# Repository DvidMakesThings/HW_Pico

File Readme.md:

# RePico

RePico is a custom-designed, feature-enhanced Raspberry Pi Pico-compatible board built for serious embedded developers. It keeps full compatibility with the RP2040 ecosystem while upgrading key components for cleaner analog performance, improved configurability, and professional-grade layout.

---

## 🔧 Key Hardware Features

- **USB-C** connector instead of Micro-USB for modern connectivity.
- **Low-noise 3.3V power supply** using `MIC5504-3.3YM5` 3.3V 300mA LDO (replaces noisy SMPS).
- **Selectable ADC Vref** via jumper:
  - External Vref input.
  - Internal precision 3.0V reference using `LM4040` + buffered by `MCP6001RT-I/OT`.
- **Selectable Vcore Supply** via jumper:
  - Use internal RP2040 regulator.
  - Or use onboard external 1.1V regulator based on `AP7335-WG-7` with adjustable output.
- **Adjustable Vcore Tuning** with trimpot-based feedback:

| Trimpot Resistance | Vcore Output |
|--------------------|---------------|
| 25k (max)          | ~1.00 V       |
| 12.5k (mid)        | ~1.18 V       |
| 0 Ω (min)          | ~1.24 V       |

- **128Mbit (16MB) QSPI Flash** — 4x more than the standard Pico.
- **RESET** and **BOOT** buttons included onboard.
- **4-layer impedance-controlled PCB** for signal integrity.

---

## PCB Stackup

- **Total Layers:** 4
- **Finished Thickness:** ~1.56 mm ±10%
- **Outer Copper Weight:** 1 oz
- **Inner Copper Weight:** 0.5 oz
- **Material:** JLC04161H-3313 (FR4)

### Layer Stackup

| Layer | Description       | Material                    | Thickness (mm) |
|-------|-------------------|-----------------------------|----------------|
| L1    | Signal (Top)      | Outer Copper 1 oz           | 0.0350         |
|       | Prepreg           | 3313 RC57%, 4.2 mil         | 0.0994         |
| L2    | Internal Plane    | Inner Copper 0.5 oz         | 0.0152         |
|       | Core              | 1.3 mm H/HOZ with copper     | 1.2650         |
| L3    | Internal Plane    | Inner Copper 0.5 oz         | 0.0152         |
|       | Prepreg           | 3313 RC57%, 4.2 mil         | 0.0994         |
| L4    | Signal (Bottom)   | Outer Copper 1 oz           | 0.0350         |
|       | **Total Thickness** |                             | **1.5588 mm**  |

---

## 📏 Controlled Impedance Configuration

| Impedance (Ω) | Type                     | Signal Layer | Top Ref | Bottom Ref | Trace Width (mm) | Trace Spacing (mm) | Trace to Copper (mm) |
|---------------|--------------------------|--------------|---------|-------------|-------------------|---------------------|-----------------------|
| 50            | Coplanar Single Ended    | L1           | /       | L2          | 0.1486            | /                   | 0.2032                |
| 90            | Coplanar Differential    | L1           | /       | L2          | 0.1488            | 0.1778              | 0.2032                |
| 90            | Coplanar Differential    | L4           | L3      | /           | 0.1488            | 0.1778              | 0.2032                |
| 50            | Coplanar Single Ended    | L4           | L3      | /           | 0.1486            | /                   | 0.2032                |

---

## 🧠 RP2040 Pinout Compatibility

All RP2040 GPIOs are exposed through 2.54mm castellated headers, maintaining full compatibility with the original Raspberry Pi Pico pinout. 

---

## Misc: Core Voltage & Overclocking

To overclock the MCU, it's possible to supply more than 1.1 V to the core.  
By default, **external core voltage generation** is enabled using the **AP7335-WG-7**, which is activated via **J1**.  
The output voltage is set by adjusting the **R1 trimpot**.

> ⚠️ It is safe — the voltage range is limited by design and cannot damage the MCU.

### Voltage Range (Set by Divider)

| R1 (Trimpot) | Total Resistance (R28 + R1) | VOUT (approx) |
|--------------|----------------------------|----------------|
| 25 kΩ (max)  | 47 kΩ                       | 1.02 V         |
| 12.5 kΩ      | 34.5 kΩ                     | 1.14 V         |
| 0 Ω (min)    | 22 kΩ                       | 1.22 V         |

### Use Cases

- **Low Power Mode:** R1 = 25 kΩ → ~1.02 V  
- **Default / Safe:** R1 = 12.5 kΩ → ~1.14 V  
- **High Performance / Overclocking:** R1 = 0 Ω → ~1.22 V  

### VOUT Behavior Across Temperatures and Trim Settings

The AP7335-WG-7 regulator is affected by temperature-dependent reference voltage (VREF), output voltage accuracy, and resistor tolerances.  
This section outlines the **worst-case VOUT values** at cold, normal, and hot temperatures, across all trimpot settings.

> ⚙️ **Calculation Parameters:**
> - VOUT Accuracy: ±2% (from AP7335-WG-7 datasheet)
> - VREF Variation: Based on VREF vs. Temperature graph  
>   - −50 °C → 0.89 V  
>   - 25 °C → 0.80 V  
>   - 125 °C → 0.782 V
> - Resistors used: 1% tolerance (R27 = 12 kΩ, R28 = 22 kΩ, R1 = 0–25 kΩ trimpot)

The RP2040's **absolute maximum core voltage is 1.3 V** — values exceeding this may cause damage.

---

### ❄️ Cold (–50 °C, VREF = 0.89 V)

**Max Trim (R1 = 25 kΩ, Rb = 47 kΩ)**  
VOUT: **1.090 V – 1.144 V** ✅ Safe

**Mid Trim (R1 = 12.5 kΩ, Rb = 34.5 kΩ)**  
VOUT: **1.170 V – 1.230 V** ✅ Safe

**Min Trim (R1 = 0 Ω, Rb = 22 kΩ)**  
VOUT: **1.339 V – 1.413 V** ❌ Danger – exceeds RP2040 1.3 V limit

---

### 🌤️ Normal (25 °C, VREF = 0.80 V)

**Max Trim (R1 = 25 kΩ, Rb = 47 kΩ)**  
VOUT: **0.980 V – 1.029 V** ✅ Safe

**Mid Trim (R1 = 12.5 kΩ, Rb = 34.5 kΩ)**  
VOUT: **1.051 V – 1.106 V** ✅ Safe

**Min Trim (R1 = 0 Ω, Rb = 22 kΩ)**  
VOUT: **1.201 V – 1.265 V** ✅ Safe

---

### 🔥 Hot (125 °C, VREF = 0.782 V)

**Max Trim (R1 = 25 kΩ, Rb = 47 kΩ)**  
VOUT: **0.958 V – 1.005 V** ✅ Safe

**Mid Trim (R1 = 12.5 kΩ, Rb = 34.5 kΩ)**  
VOUT: **1.028 V – 1.082 V** ✅ Safe

**Min Trim (R1 = 0 Ω, Rb = 22 kΩ)**  
VOUT: **1.180 V – 1.243 V** ✅ Safe

## License
This project is licensed under the GPL-3.0 License. See the [LICENSE](LICENSE) file for details.

## Contact
For questions or feedback:
- Email: [dvidmakesthing@gmail.com](mailto:dvidmakesthing@gmail.com)
- GitHub: [DvidMakesThings](https://github.com/DvidMakesThings)

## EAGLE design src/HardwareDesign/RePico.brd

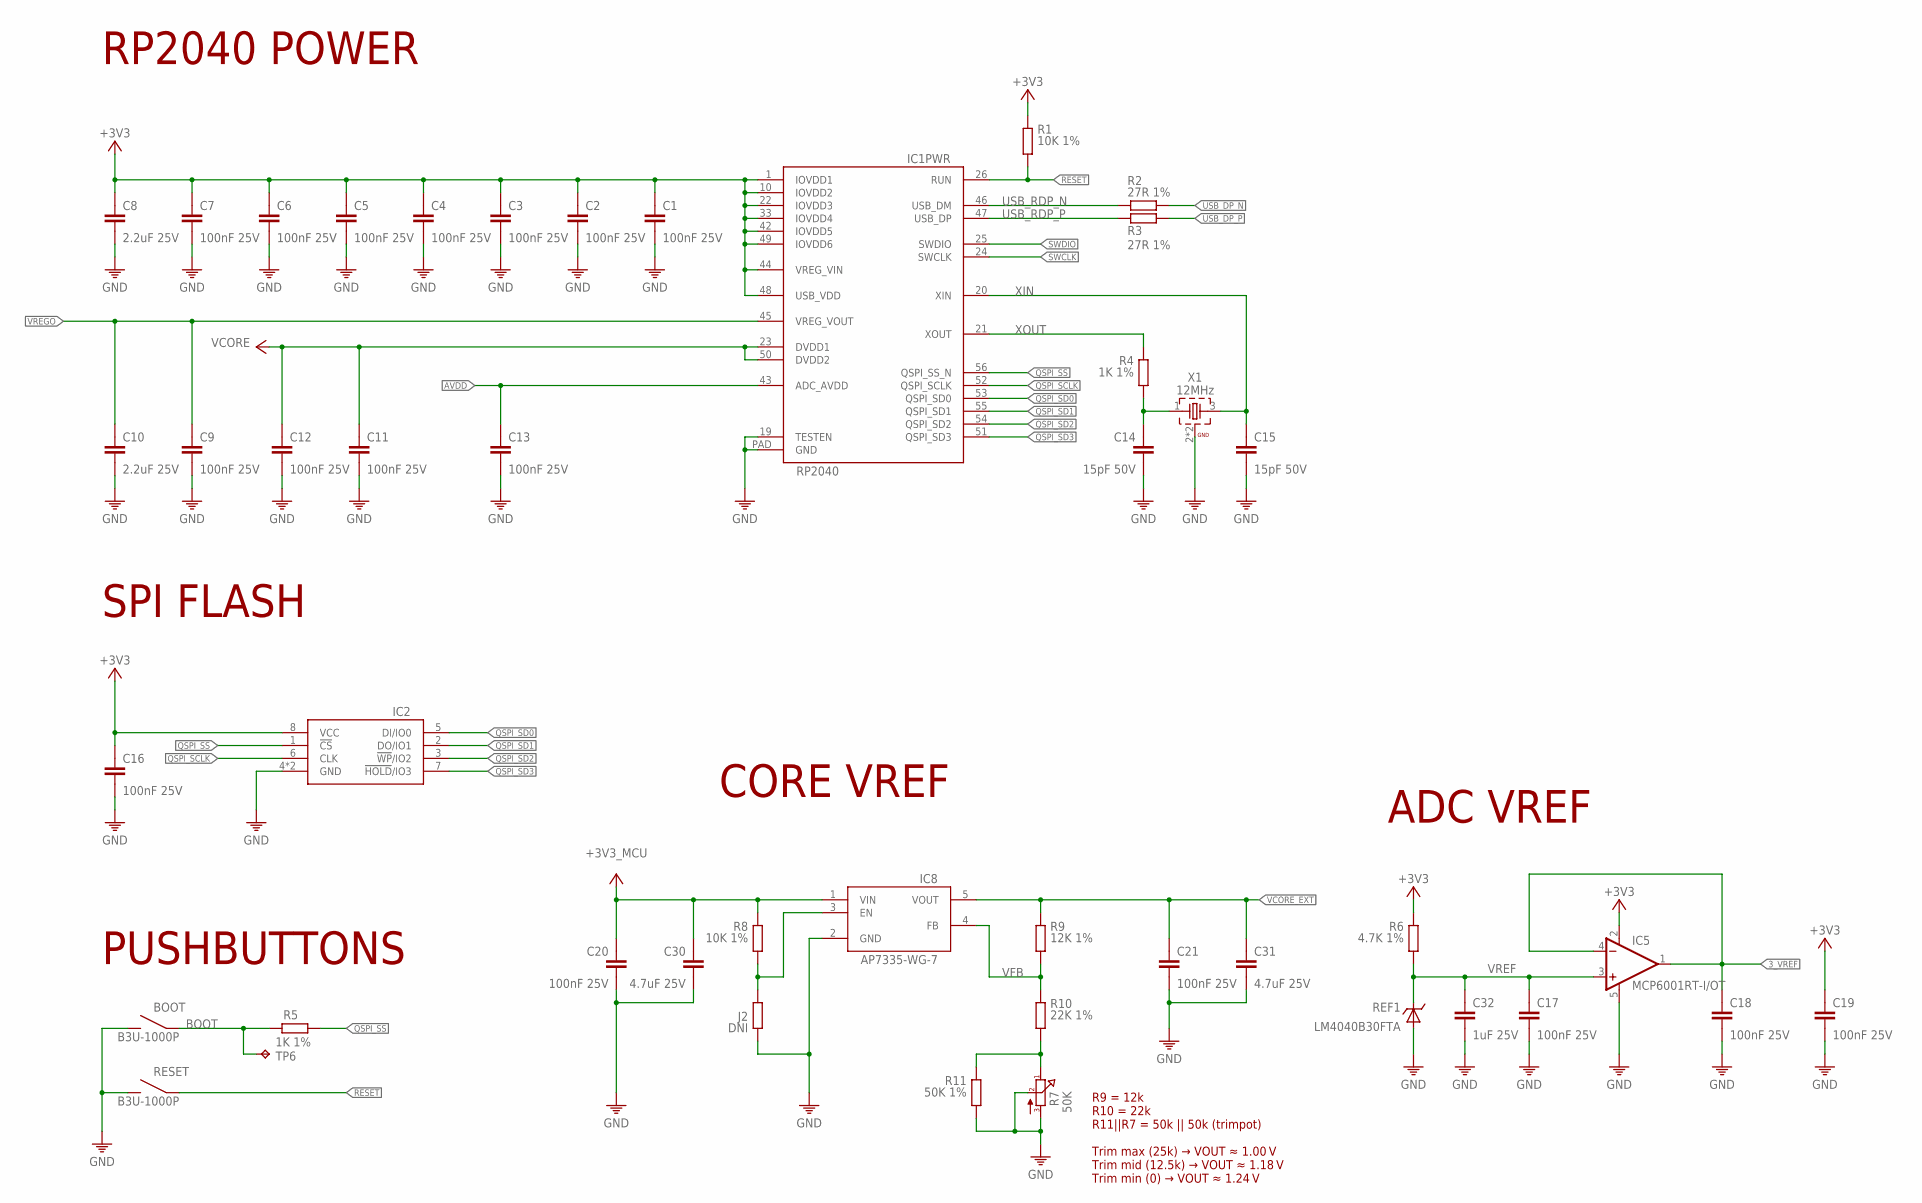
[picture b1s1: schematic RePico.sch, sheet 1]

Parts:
BOOT: B3U-1000P
C1, C2, C3, C4, C5, C6, C7, C9, C11, C12, C13, C16, C17, C18, C19, C20, C21: 100nF 25V; 0201
C8, C10: 2.2uF 25V; 0402
C14, C15: 15pF 50V; 0201
C30, C31: 4.7uF 25V; 0402
C32: 1uF 25V; 0402
IC1: RP2040; QFN56
IC2: W25Q128JVP; SON127P600X500X75-8N
IC5: MCP6001RT-I/OT; SOT23-5
IC8: AP7335-WG-7; SOT23-5
J2: DNI; R0201
R1, R8: 10K 1%; 0201
R2, R3: 27R 1%; 0201
R4, R5: 1K 1%; 0201
R6: 4.7K 1%; 0402
R7: 50K; SMD_TRIMM
R9: 12K 1%; 0201
R10: 22K 1%; 0201
R11: 50K 1%; 0402
REF1: LM4040B30FTA; SOT23
RESET: B3U-1000P
TP6: TPB1,27; B1,27
X1: 12MHz; WE-XTAL_CFPX-180

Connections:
3_VREF: C18.1, IC5.1 (OUT), IC5.4 (-IN); also elsewhere on the board
+3V3: C1.1, C2.1, C3.1, C4.1, C5.1, C6.1, C7.1, C8.1, C16.1, C19.1, IC1.1 (IOVDD1), IC1.10 (IOVDD2), IC1.22 (IOVDD3), IC1.33 (IOVDD4), IC1.42 (IOVDD5), IC1.44 (VREG_VIN), IC1.48 (USB_VDD), IC1.49 (IOVDD6), IC2.8 (VCC), IC5.2 (V+), R1.1, R6.1; also elsewhere on the board
+3V3_MCU: C20.1, C30.1, IC8.1 (VIN), R8.1
AVDD: C13.1, IC1.43 (ADC_AVDD); also elsewhere on the board
BOOT: BOOT.1, R5.1, TP6.TP
FBTRIM: R7.1, R10.2, R11.1
GND: BOOT.2, C1.2, C2.2, C3.2, C4.2, C5.2, C6.2, C7.2, C8.2, C9.2, C10.2, C11.2, C12.2, C13.2, C14.2, C15.2, C16.2, C17.2, C18.2, C19.2, C20.2, C21.2, C30.2, C31.2, C32.2, IC1.19 (TESTEN), IC1.PAD (GND), IC2.4 (GND), IC2.PAD (GND), IC5.5 (V-), IC8.2 (GND), J2.2, R7.2, R7.3, R11.2, REF1.2 (A), REF1.3 (A), RESET.2, X1.2 (GND), X1.4 (GND); also elsewhere on the board
unnamed: IC8.3 (EN), J2.1, R8.2
QSPI_SCLK: IC1.52 (QSPI_SCLK), IC2.6 (CLK)
QSPI_SD0: IC1.53 (QSPI_SD0), IC2.5 (DI/IO0)
QSPI_SD1: IC1.55 (QSPI_SD1), IC2.2 (DO/IO1)
QSPI_SD2: IC1.54 (QSPI_SD2), IC2.3 (!WP!/IO2)
QSPI_SD3: IC1.51 (QSPI_SD3), IC2.7 (!HOLD!/IO3)
QSPI_SS: IC1.56 (QSPI_SS_N), IC2.1 (!CS), R5.2
RESET: IC1.26 (RUN), R1.2, RESET.1; also elsewhere on the board
SWCLK: IC1.24 (SWCLK); also elsewhere on the board
SWDIO: IC1.25 (SWDIO); also elsewhere on the board
USB_DP_N: R2.2; also elsewhere on the board
USB_DP_P: R3.2; also elsewhere on the board
USB_RDP_N: IC1.46 (USB_DM), R2.1
USB_RDP_P: IC1.47 (USB_DP), R3.1
VCORE: C11.1, C12.1, IC1.23 (DVDD1), IC1.50 (DVDD2); also elsewhere on the board
VCORE_EXT: C21.1, C31.1, IC8.5 (VOUT), R9.1; also elsewhere on the board
VFB: IC8.4 (FB), R9.2, R10.1
VREF: C17.1, C32.1, IC5.3 (+IN), R6.2, REF1.1 (C)
VREGO: C9.1, C10.1, IC1.45 (VREG_VOUT); also elsewhere on the board
XIN: C15.1, IC1.20 (XIN), X1.3 (2)
XOUT: IC1.21 (XOUT), R4.1
XO_R: C14.1, R4.2, X1.1

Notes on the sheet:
RP2040 POWER
SPI FLASH
PUSHBUTTONS
ADC VREF
CORE VREF
R9 = 12k R10 = 22k R11||R7 = 50k || 50k (trimpot) Trim max (25k) → VOUT ≈ 1.00 V Trim mid (12.5k) → VOUT ≈ 1.18 V Trim min (0) → VOUT ≈ 1.24 V

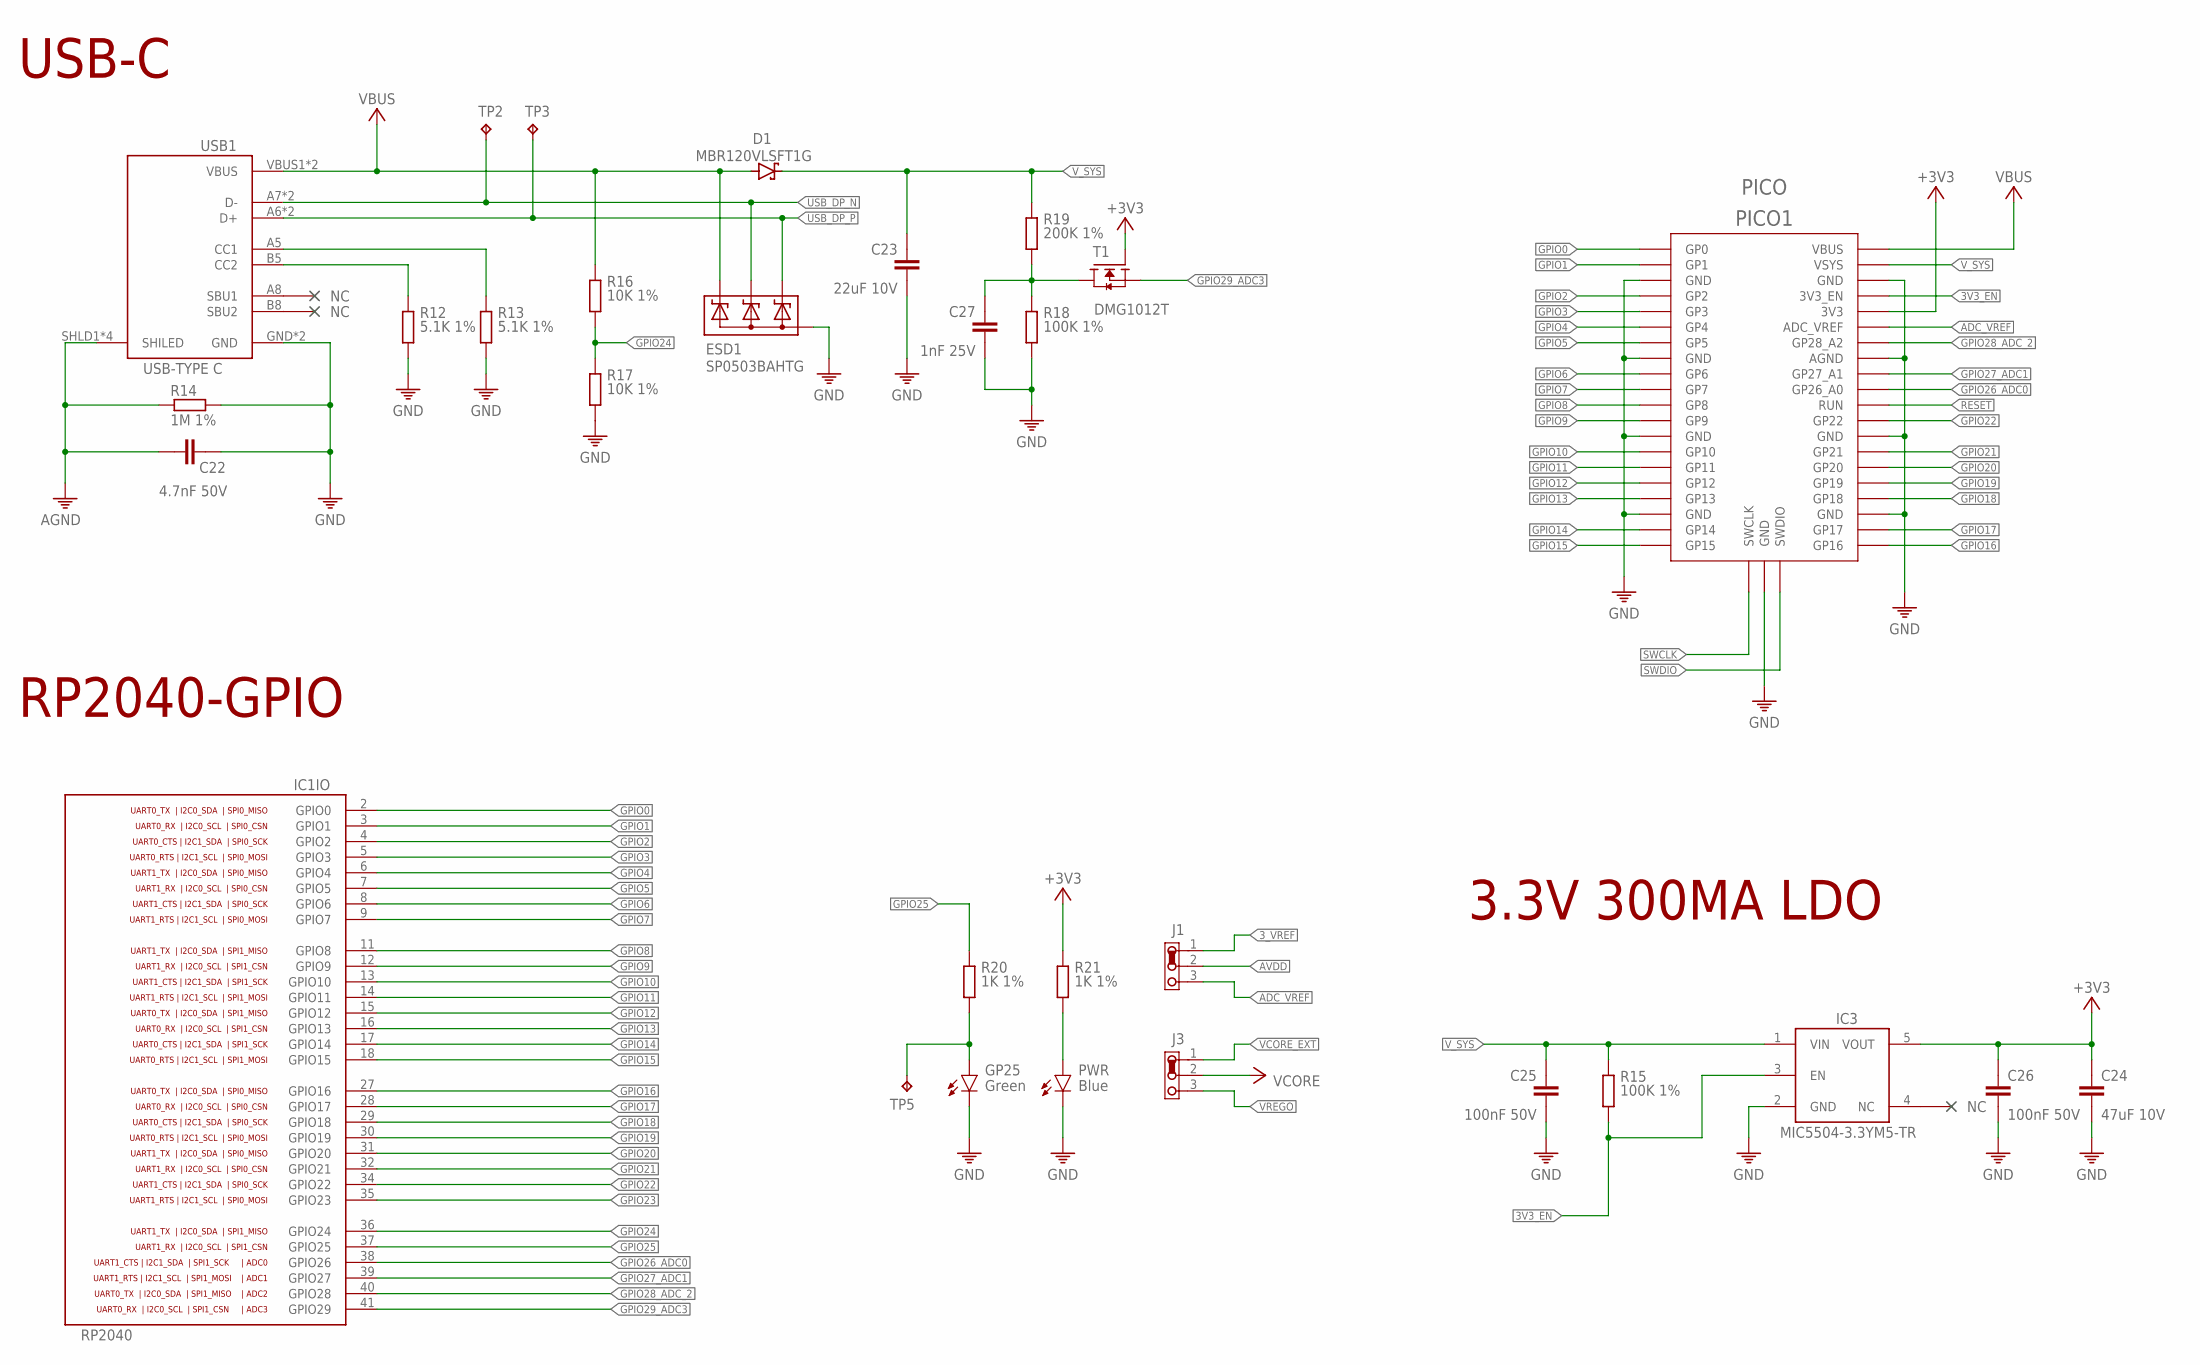
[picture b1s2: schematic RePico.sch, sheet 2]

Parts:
C22: 4.7nF 50V; 0603
C23: 22uF 10V; 0603
C24: 47uF 10V; 0805
C25, C26: 100nF 50V; 0402
C27: 1nF 25V; 0201
D1: MBR120VLSFT1G; SOD-123
ESD1: SP0503BAHTG; SOT143
GP25: Green; LED-0603
IC1: RP2040; QFN56
IC3: MIC5504-3.3YM5; SOT23-5
J1, J3: JUMPER-3
PICO1: PICO
PWR: Blue; LED-0603
R12, R13: 5.1K 1%; 0201
R14: 1M 1%; 0603
R15, R18: 100K 1%; 0201
R16, R17: 10K 1%; 0201
R19: 200K 1%; 0201
R20, R21: 1K 1%; 0402
T1: DMG1012T; SOT23
TP2, TP3, TP5: TPB1,27; B1,27
USB1: USB-TYPE-C-018; USB-C

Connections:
3V3_EN: IC3.3 (EN), PICO1.3V3_EN, PICO1.3VE (3V3_EN), R15.2
3_VREF: J1.1; also elsewhere on the board
+3V3: C24.1, C26.1, IC3.5 (VOUT), PICO1.3V (3V3), PICO1.3V3, R21.1, T1.1 (G); also elsewhere on the board
ADC_VREF: J1.3, PICO1.ADC_VREF, PICO1.AVR (ADC_VREF)
AGND: C22.1, R14.1, USB1.SHLD1 (SHILED), USB1.SHLD2 (SHILED), USB1.SHLD3 (SHILED), USB1.SHLD4 (SHILED)
AVDD: J1.2; also elsewhere on the board
GND: C22.2, C23.2, C24.2, C25.2, C26.2, C27.2, ESD1.1 (A), GP25.C, IC3.2 (GND), PICO1.AGN (AGND), PICO1.AGND, PICO1.G@1 (GND), PICO1.G@2 (GND), PICO1.G@3 (GND), PICO1.G@4 (GND), PICO1.G@5 (GND), PICO1.G@6 (GND), PICO1.G@7 (GND), PICO1.G@8 (GND), PICO1.GND@1 (GND), PICO1.GND@2 (GND), PICO1.GND@3 (GND), PICO1.GND@4 (GND), PICO1.GND@5 (GND), PICO1.GND@6 (GND), PICO1.GND@7 (GND), PICO1.GND@8 (GND), PWR.C, R12.2, R13.2, R14.2, R17.2, R18.2, USB1.GND, USB1.GND2 (GND); also elsewhere on the board
GPIO0: IC1.2 (GPIO0), PICO1.0 (GP0), PICO1.GP0
GPIO1: IC1.3 (GPIO1), PICO1.1 (GP1), PICO1.GP1
GPIO2: IC1.4 (GPIO2), PICO1.2 (GP2), PICO1.GP2
GPIO3: IC1.5 (GPIO3), PICO1.3 (GP3), PICO1.GP3
GPIO4: IC1.6 (GPIO4), PICO1.4 (GP4), PICO1.GP4
GPIO5: IC1.7 (GPIO5), PICO1.5 (GP5), PICO1.GP5
GPIO6: IC1.8 (GPIO6), PICO1.6 (GP6), PICO1.GP6
GPIO7: IC1.9 (GPIO7), PICO1.7 (GP7), PICO1.GP7
GPIO8: IC1.11 (GPIO8), PICO1.8 (GP8), PICO1.GP8
GPIO9: IC1.12 (GPIO9), PICO1.9 (GP9), PICO1.GP9
GPIO10: IC1.13 (GPIO10), PICO1.10 (GP10), PICO1.GP10
GPIO11: IC1.14 (GPIO11), PICO1.11 (GP11), PICO1.GP11
GPIO12: IC1.15 (GPIO12), PICO1.12 (GP12), PICO1.GP12
GPIO13: IC1.16 (GPIO13), PICO1.13 (GP13), PICO1.GP13
GPIO14: IC1.17 (GPIO14), PICO1.14 (GP14), PICO1.GP14
GPIO15: IC1.18 (GPIO15), PICO1.15 (GP15), PICO1.GP15
GPIO16: IC1.27 (GPIO16), PICO1.16 (GP16), PICO1.GP16
GPIO17: IC1.28 (GPIO17), PICO1.17 (GP17), PICO1.GP17
GPIO18: IC1.29 (GPIO18), PICO1.18 (GP18), PICO1.GP18
GPIO19: IC1.30 (GPIO19), PICO1.19 (GP19), PICO1.GP19
GPIO20: IC1.31 (GPIO20), PICO1.20 (GP20), PICO1.GP20
GPIO21: IC1.32 (GPIO21), PICO1.21 (GP21), PICO1.GP21
GPIO22: IC1.34 (GPIO22), PICO1.22 (GP22), PICO1.GP22
GPIO23: IC1.35 (GPIO23)
GPIO24: IC1.36 (GPIO24), R16.2, R17.1
GPIO25: IC1.37 (GPIO25), R20.1
GPIO26_ADC0: IC1.38 (GPIO26), PICO1.26 (GP26_A0), PICO1.GP26_A0
GPIO27_ADC1: IC1.39 (GPIO27), PICO1.27 (GP27_A1), PICO1.GP27_A1
GPIO28_ADC_2: IC1.40 (GPIO28), PICO1.28 (GP28_A2), PICO1.GP28_A2
GPIO29_ADC3: IC1.41 (GPIO29), T1.2 (S)
unnamed: R13.1, USB1.A5 (CC1)
unnamed: R12.1, USB1.B5 (CC2)
unnamed: C27.1, R18.1, R19.2, T1.3 (D)
unnamed: GP25.A, R20.2, TP5.TP
unnamed: PWR.A, R21.2
RESET: PICO1.R (RUN), PICO1.RUN; also elsewhere on the board
SWCLK: PICO1.SWC (SWCLK), PICO1.SWCLK; also elsewhere on the board
SWDIO: PICO1.SWD (SWDIO), PICO1.SWDIO; also elsewhere on the board
USB_DP_N: ESD1.3 (C2), TP2.TP, USB1.A7 (D-), USB1.B7 (D-); also elsewhere on the board
USB_DP_P: ESD1.2 (C1), TP3.TP, USB1.A6 (D+), USB1.B6 (D+); also elsewhere on the board
VBUS: D1.A, ESD1.4 (C3), PICO1.VBU (VBUS), PICO1.VBUS, R16.1, USB1.VBUS1 (VBUS), USB1.VBUS2 (VBUS)
VCORE: J3.2; also elsewhere on the board
VCORE_EXT: J3.1; also elsewhere on the board
VREGO: J3.3; also elsewhere on the board
V_SYS: C23.1, C25.1, D1.C, IC3.1 (VIN), PICO1.VSY (VSYS), PICO1.VSYS, R15.1, R19.1

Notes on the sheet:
USB-C
RP2040-GPIO
3.3V 300MA LDO

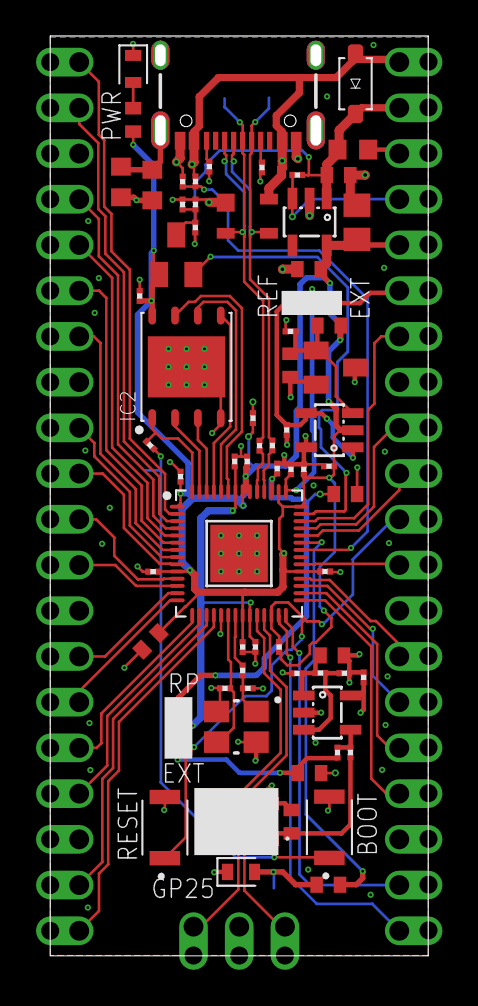
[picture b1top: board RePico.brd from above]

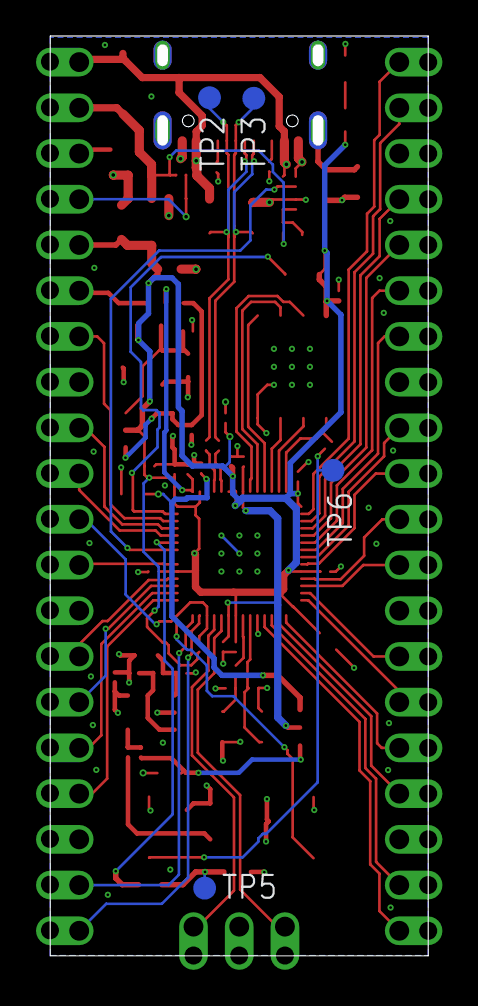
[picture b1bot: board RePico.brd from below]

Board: 4 copper layers, 21.0 x 51.1 mm, 74 parts (4 on the bottom side), 68 nets.

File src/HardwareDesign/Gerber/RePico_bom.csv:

Comment,Designator,Footprint,LCSC Part #
,IC2,SON127P600X500X75-8N,
1K 1%,R4,0201,C270365
1K 1%,R5,0201,C270365
1K 1%,R20,0402,C11702
1K 1%,R21,0402,C11702
1M 1%,R14,0603,C22935
1nF 25V,C27,0201,C7694325V
1uF 25V,C32,0402,C52923
4.7K 1%,R6,0402,C25900
4.7nF 50V,C22,0603,C53987
4.7uF 25V,C30,0402,C22367824
5.1K 1%,R12,0201,C274341
5.1K 1%,R13,0201,C274341
10K 1%,R1,0201,C473048
10K 1%,R8,0201,C473048
10K 1%,R16,0201,C473048
10K 1%,R17,0201,C473048
12K 1%,R9,0201,C270363
12MHz,X1,WE-XTAL_CFPX-180,C9002
15pF 50V,C14,0201,C22374851
15pF 50V,C15,0201,C22374851
22K 1%,R10,0201,C474416
27R 1%,R2,0201,C473051
27R 1%,R3,0201,C473051
47uF 10V,C24,0805,C6119904
50K,R7,SMD_TRIMM,C913246
50K 1%,R11,0402,C166559
100K 1%,R15,0201,C270364
100K 1%,R18,0201,C270364
100nF 25V,C1,0201,C76939
100nF 25V,C2,0201,C76939
100nF 25V,C3,0201,C76939
100nF 25V,C4,0201,C76939
100nF 25V,C5,0201,C76939
100nF 25V,C7,0201,C76939
100nF 25V,C9,0201,C76939
100nF 25V,C11,0201,C76939
100nF 25V,C12,0201,C76939
100nF 25V,C13,0201,C76939
100nF 25V,C16,0201,C76939
100nF 25V,C17,0201,C76939
100nF 25V,C18,0201,C76939
100nF 25V,C19,0201,C76939
100nF 25V,C20,0201,C76939
100nF 25V,C21,0201,C76939
100nF 50V,C25,0402,C307331
100nF 50V,C26,0402,C307331
200K 1%,R19,0201,C270357
AP7335-WG-7 ,IC8,SOT23-5,C460382
B3U-1000P ,BOOT,B3U-1000P,C231329
B3U-1000P ,RESET,B3U-1000P,C231329
Blue,PWR,LED-0603,C965807
DMG1012T,T1,SOT23,C2830301
DNI,J2,R0201,
Green,GP25,LED-0603,C965804
JUMPER-3,J1 J3,JUMPER-3,
LM4040B30FTA,REF1,SOT23,C460604
MBR120VLSFT1G,D1,SOD-123,C223608
MCP6001RT-I/OT,IC5,SOT23-5,C154973
MIC5504-3.3YM5 ,IC3,SOT23-5,C41348078
RP2040,IC1,QFN56,C2040
SP0503BAHTG,ESD1,SOT143,C3040626
USB-TYPE-C-018 ,USB1,USB-C,C2927038
2.2uF 25V,C8,0402,C385032
2.2uF 25V,C10,0402,C385032
4.7uF 25V,C31,0402,C22367824
47uF 10V,C23,0805,C6119904
100nF 25V,C6,0201,C76939
TPB1 27,TP2,B1 27,
TPB1 27,TP3,B1 27,
TPB1 27,TP5,B1 27,
TPB1 27,TP6,B1 27,

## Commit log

2025-06-08 initial creation
2025-06-08 add gerbers
